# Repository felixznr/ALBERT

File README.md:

# ALBERT

Albert I was a rhesus macaque monkey and the first mammal launched on a rocket (V-2 Rocket "Blossom No. 3") on June 18, 1948. The launch was staged at Albert I, a nine-pound monkey, was anesthetized and placed inside the rocket's crew capsule in the nose of the V-2 rocket. The flight did not reach outer space. The last couple hours before his death, Albert was lit asf on morphine

---

## Project Overview

ALBERT is a self-regulating guided rocket project developed as a Maturaprojekt (Austrian graduation project). The goal is to build a fully functional, autonomous rocket system capable of correcting its own flight path and safely recovering via parachute deployment.

**Key Objectives:**
- Develop autonomous flight path correction through advanced control systems
- Implement fin-based steering for precise guidance
- Create a reliable parachute recovery system
- Design a concept of a custom solid fuel motor
- Integrate comprehensive telemetry and safety systems

## Team Structure

- **Timofey Luzin**: Recovery system, steering system, and structural components
- **Felix Zauner**: Flight computer development, control systems, simulation, and telemetry

## Repository Organization

```
├── 1_Documentation/        # Project documentation and requirements
├── 2_CAD_Structure/        # 3D models and structural designs  
├── 3_Flight_Computer/      # Flight computer hardware
├── 4_Simulation/           # Flight simulation and testing tools
└── 5_Codebase/             # Main source code and algorithms
```

For detailed technical specifications, see `1_Documentation/Diplomarbeit_ALBERT/chapter/main.pdf`.

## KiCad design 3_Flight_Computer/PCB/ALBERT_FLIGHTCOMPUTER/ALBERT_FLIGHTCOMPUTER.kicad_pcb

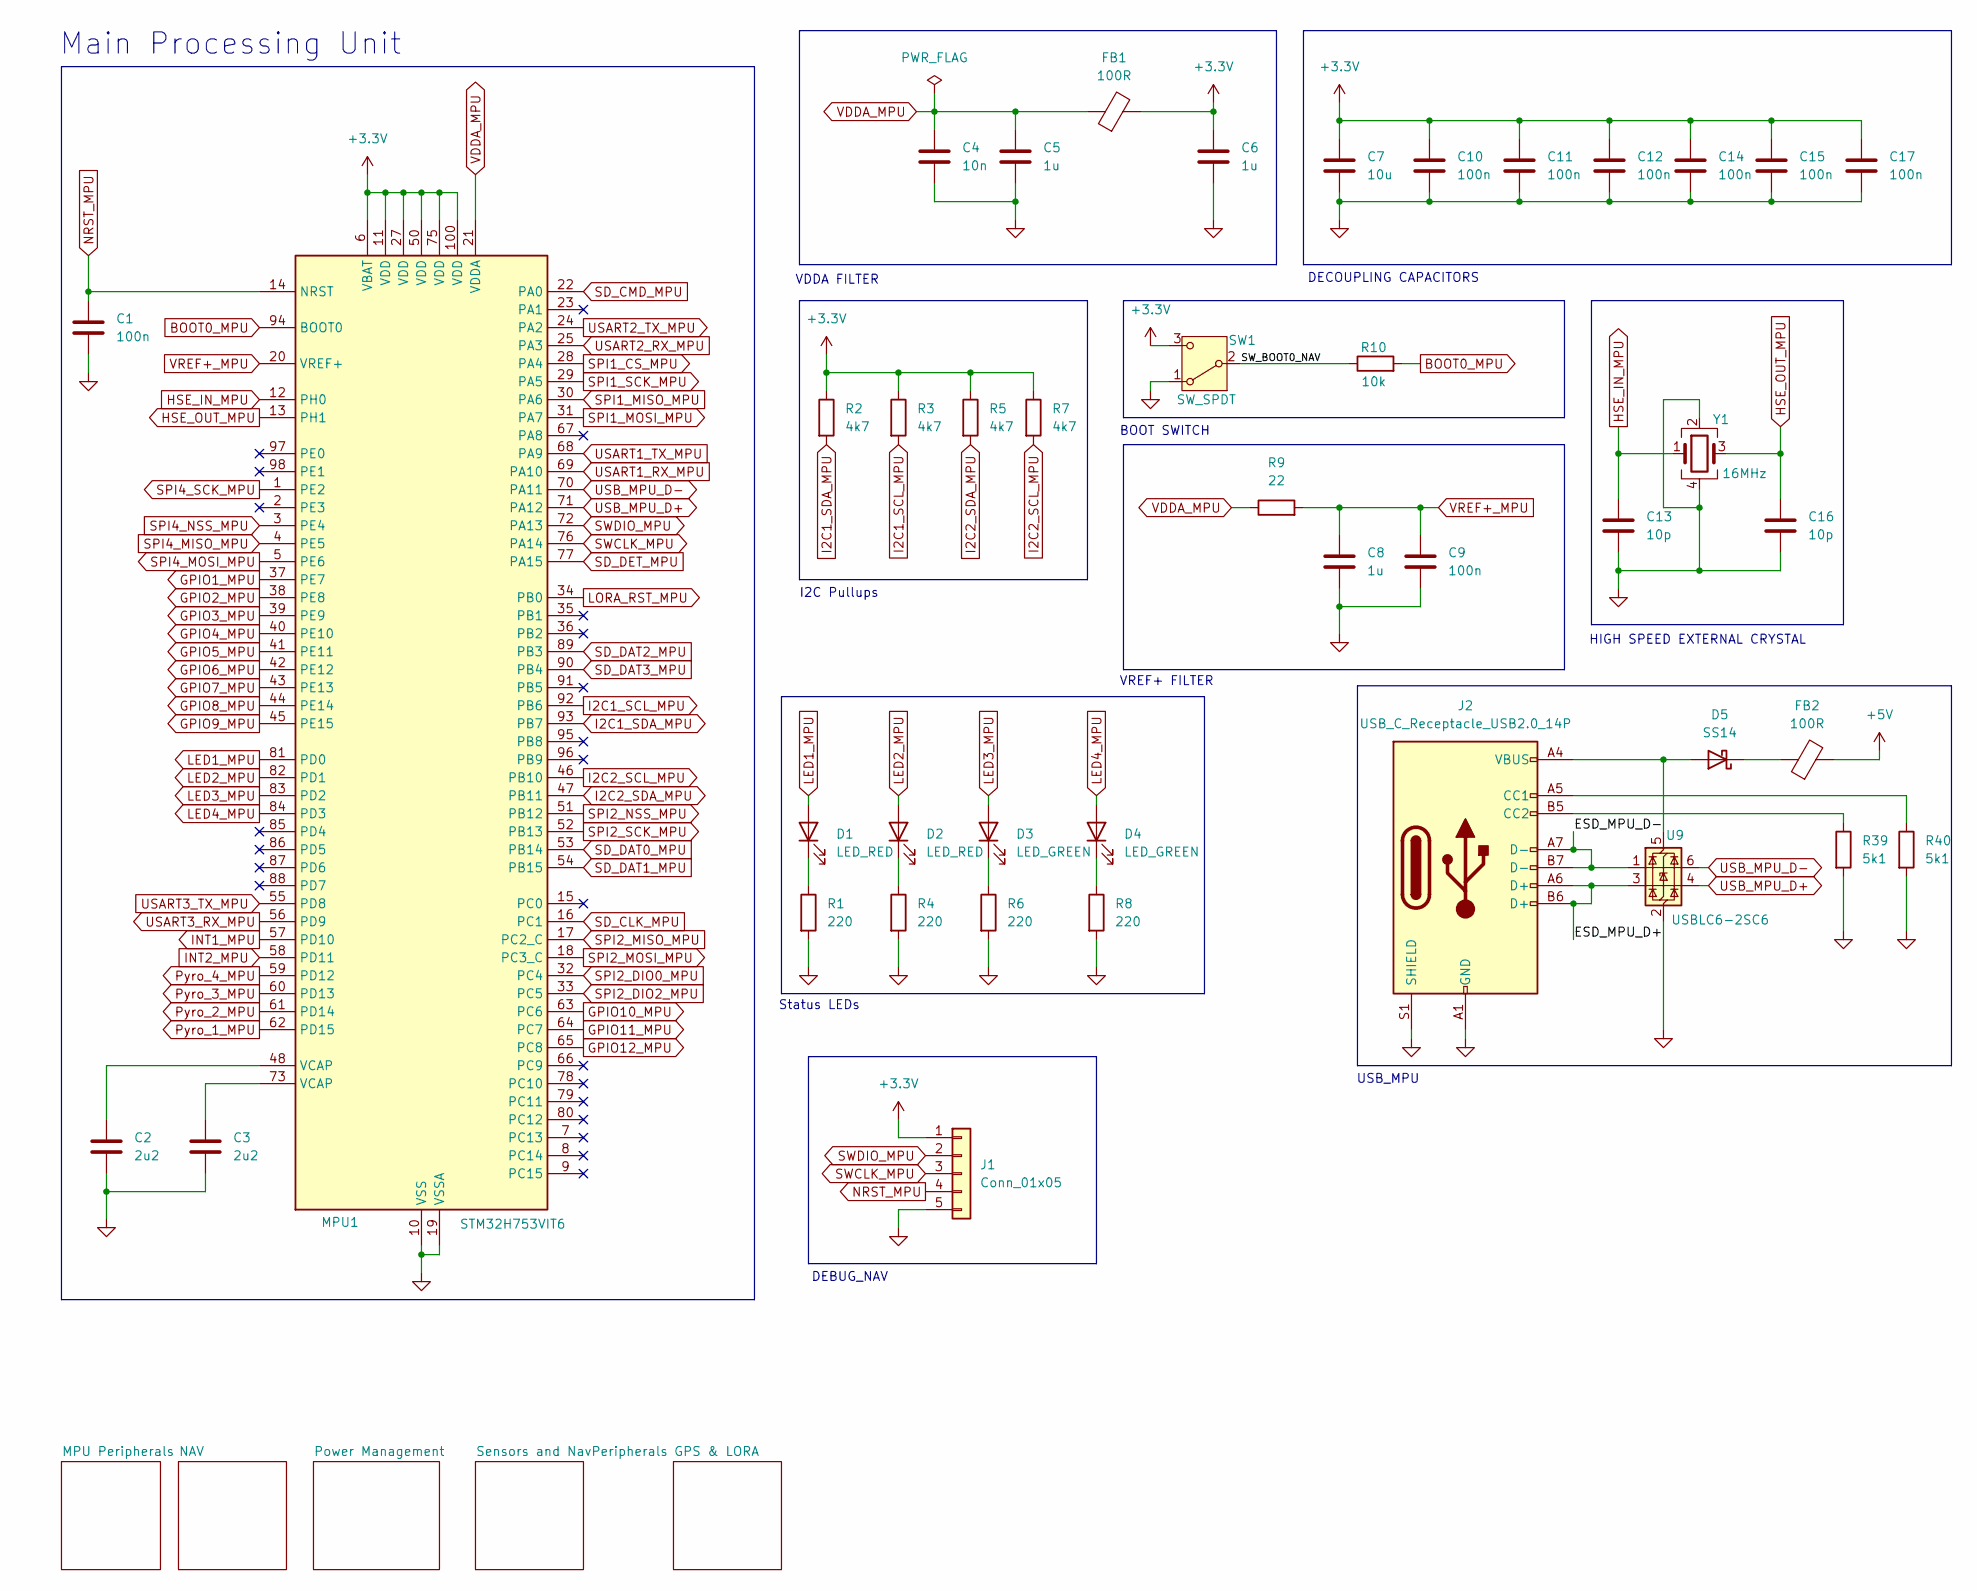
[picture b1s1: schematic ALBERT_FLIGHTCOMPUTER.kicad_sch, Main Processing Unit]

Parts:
C1, C9, C10, C11, C12, C14, C15, C17: 100n; C_0402_1005Metric; LCSC C1525
C2, C3: 2u2; C_0805_2012Metric; LCSC C377773
C4: 10n; C_0402_1005Metric; LCSC C15195
C5, C6, C8: 1u; C_0805_2012Metric; LCSC C28323
C7: 10u; C_0805_2012Metric; LCSC C15850
C13, C16: 10p; C_0402_1005Metric; LCSC C32949
D1, D2: LED_RED; LED_0603_1608Metric
D3, D4: LED_GREEN; LED_0603_1608Metric
D5: SS14; D_SMA; LCSC C2480
FB1: 100R; L_0603_1608Metric; LCSC C15957
FB2: 100R; L_0805_2012Metric; LCSC C15957
J1: Conn_01x05; PinHeader_1x05_P2.54mm_Vertical
J2: USB_C_Receptacle_USB2.0_14P; USB_C_Receptacle_HRO_TYPE-C-31-M-12; LCSC C165948
MPU1: STM32H753VIT6; LQFP-100_14x14mm_P0.5mm; Manufacturer Part Number STM32H753VIT6; LCSC C730206
R1, R4, R6, R8: 220; R_0402_1005Metric; LCSC C25091
R2, R3, R5, R7: 4k7; R_0402_1005Metric; LCSC C25900
R9: 22; R_0402_1005Metric; LCSC C25092
R10: 10k; R_0402_1005Metric; LCSC C25744
R39, R40: 5k1; R_0402_1005Metric; LCSC C25905
SW1: SW_SPDT; SW_SPDT_PCM12; LCSC C221841
U9: USBLC6-2SC6; SOT-23-6; LCSC C7519
Y1: 16MHz; Crystal_SMD_3225-4Pin_3.2x2.5mm; LCSC C13738

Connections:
+3.3V: C6.1, C7.1, C10.1, C11.1, C12.1, C14.1, C15.1, C17.1, FB1.2, J1.1, MPU1.6 (VBAT), MPU1.11 (VDD), MPU1.27 (VDD), MPU1.50 (VDD), MPU1.75 (VDD), MPU1.100 (VDD), R2.1, R3.1, R5.1, R7.1, SW1.3 (C); also elsewhere on the board
+5V: FB2.2; also elsewhere on the board
/ESD_MPU_D+: J2.A6 (D+), J2.B6 (D+), U9.3 (I/O2)
/ESD_MPU_D-: J2.A7 (D-), J2.B7 (D-), U9.1 (I/O1)
/SW_BOOT0_NAV: R10.1, SW1.2 (B)
BOOT0_MPU: MPU1.94 (BOOT0), R10.2
GND: C1.2, C2.2, C3.2, C4.2, C5.2, C6.2, C7.2, C8.2, C9.2, C10.2, C11.2, C12.2, C13.2, C14.2, C15.2, C16.2, C17.2, J1.5, J2.A1 (GND), J2.A12 (GND), J2.B1 (GND), J2.B12 (GND), J2.S1 (SHIELD), MPU1.10 (VSS), MPU1.19 (VSSA), MPU1.26 (VSS), MPU1.49 (VSS), MPU1.74 (VSS), MPU1.99 (VSS), R1.2, R4.2, R6.2, R8.2, R39.2, R40.2, SW1.1 (A), U9.2 (GND), Y1.2, Y1.4; also elsewhere on the board
GPIO1_MPU: MPU1.37 (PE7); also elsewhere on the board
GPIO2_MPU: MPU1.38 (PE8); also elsewhere on the board
GPIO3_MPU: MPU1.39 (PE9); also elsewhere on the board
GPIO4_MPU: MPU1.40 (PE10); also elsewhere on the board
GPIO5_MPU: MPU1.41 (PE11); also elsewhere on the board
GPIO6_MPU: MPU1.42 (PE12); also elsewhere on the board
GPIO7_MPU: MPU1.43 (PE13); also elsewhere on the board
GPIO8_MPU: MPU1.44 (PE14); also elsewhere on the board
GPIO9_MPU: MPU1.45 (PE15); also elsewhere on the board
GPIO10_MPU: MPU1.63 (PC6); also elsewhere on the board
GPIO11_MPU: MPU1.64 (PC7); also elsewhere on the board
GPIO12_MPU: MPU1.65 (PC8); also elsewhere on the board
HSE_IN_MPU: C13.1, MPU1.12 (PH0), Y1.1
HSE_OUT_MPU: C16.1, MPU1.13 (PH1), Y1.3
I2C1_SCL_MPU: MPU1.92 (PB6), R3.2; also elsewhere on the board
I2C1_SDA_MPU: MPU1.93 (PB7), R2.2; also elsewhere on the board
I2C2_SCL_MPU: MPU1.46 (PB10), R7.2; also elsewhere on the board
I2C2_SDA_MPU: MPU1.47 (PB11), R5.2; also elsewhere on the board
INT1_MPU: MPU1.57 (PD10); also elsewhere on the board
INT2_MPU: MPU1.58 (PD11); also elsewhere on the board
LED1_MPU: D1.2 (A), MPU1.81 (PD0)
LED2_MPU: D2.2 (A), MPU1.82 (PD1)
LED3_MPU: D3.2 (A), MPU1.83 (PD2)
LED4_MPU: D4.2 (A), MPU1.84 (PD3)
LORA_RST_MPU: MPU1.34 (PB0); also elsewhere on the board
NRST_MPU: C1.1, J1.4, MPU1.14 (NRST)
unnamed: C2.1, MPU1.48 (VCAP)
unnamed: C3.1, MPU1.73 (VCAP)
unnamed: D1.1 (K), R1.1
unnamed: D2.1 (K), R4.1
unnamed: D3.1 (K), R6.1
unnamed: D4.1 (K), R8.1
unnamed: D5.2 (A), J2.A4 (VBUS), J2.A9 (VBUS), J2.B4 (VBUS), J2.B9 (VBUS), U9.5 (VBUS)
unnamed: D5.1 (K), FB2.1
unnamed: J2.A5 (CC1), R40.1
unnamed: J2.B5 (CC2), R39.1
Pyro_1_MPU: MPU1.62 (PD15); also elsewhere on the board
Pyro_2_MPU: MPU1.61 (PD14); also elsewhere on the board
Pyro_3_MPU: MPU1.60 (PD13); also elsewhere on the board
Pyro_4_MPU: MPU1.59 (PD12); also elsewhere on the board
SD_CLK_MPU: MPU1.16 (PC1); also elsewhere on the board
SD_CMD_MPU: MPU1.22 (PA0); also elsewhere on the board
SD_DAT0_MPU: MPU1.53 (PB14); also elsewhere on the board
SD_DAT1_MPU: MPU1.54 (PB15); also elsewhere on the board
SD_DAT2_MPU: MPU1.89 (PB3); also elsewhere on the board
SD_DAT3_MPU: MPU1.90 (PB4); also elsewhere on the board
SD_DET_MPU: MPU1.77 (PA15); also elsewhere on the board
SPI1_CS_MPU: MPU1.28 (PA4); also elsewhere on the board
SPI1_MISO_MPU: MPU1.30 (PA6); also elsewhere on the board
SPI1_MOSI_MPU: MPU1.31 (PA7); also elsewhere on the board
SPI1_SCK_MPU: MPU1.29 (PA5); also elsewhere on the board
SPI2_DIO0_MPU: MPU1.32 (PC4); also elsewhere on the board
SPI2_DIO2_MPU: MPU1.33 (PC5); also elsewhere on the board
SPI2_MISO_MPU: MPU1.17 (PC2_C); also elsewhere on the board
SPI2_MOSI_MPU: MPU1.18 (PC3_C); also elsewhere on the board
SPI2_NSS_MPU: MPU1.51 (PB12); also elsewhere on the board
SPI2_SCK_MPU: MPU1.52 (PB13); also elsewhere on the board
SPI4_MISO_MPU: MPU1.4 (PE5); also elsewhere on the board
SPI4_MOSI_MPU: MPU1.5 (PE6); also elsewhere on the board
SPI4_NSS_MPU: MPU1.3 (PE4); also elsewhere on the board
SPI4_SCK_MPU: MPU1.1 (PE2); also elsewhere on the board
SWCLK_MPU: J1.3, MPU1.76 (PA14)
SWDIO_MPU: J1.2, MPU1.72 (PA13)
USART1_RX_MPU: MPU1.69 (PA10); also elsewhere on the board
USART1_TX_MPU: MPU1.68 (PA9); also elsewhere on the board
USART2_RX_MPU: MPU1.25 (PA3); also elsewhere on the board
USART2_TX_MPU: MPU1.24 (PA2); also elsewhere on the board
USART3_RX_MPU: MPU1.56 (PD9); also elsewhere on the board
USART3_TX_MPU: MPU1.55 (PD8); also elsewhere on the board
USB_MPU_D+: MPU1.71 (PA12), U9.4 (I/O2)
USB_MPU_D-: MPU1.70 (PA11), U9.6 (I/O1)
VDDA_MPU: C4.1, C5.1, FB1.1, MPU1.21 (VDDA), R9.1
VREF+_MPU: C8.1, C9.1, MPU1.20 (VREF+), R9.2

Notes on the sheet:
USB_MPU
BOOT SWITCH
VDDA FILTER
Main Processing Unit
VREF+ FILTER
I2C Pullups
DEBUG_NAV
HIGH SPEED EXTERNAL CRYSTAL
Status LEDs
DECOUPLING CAPACITORS

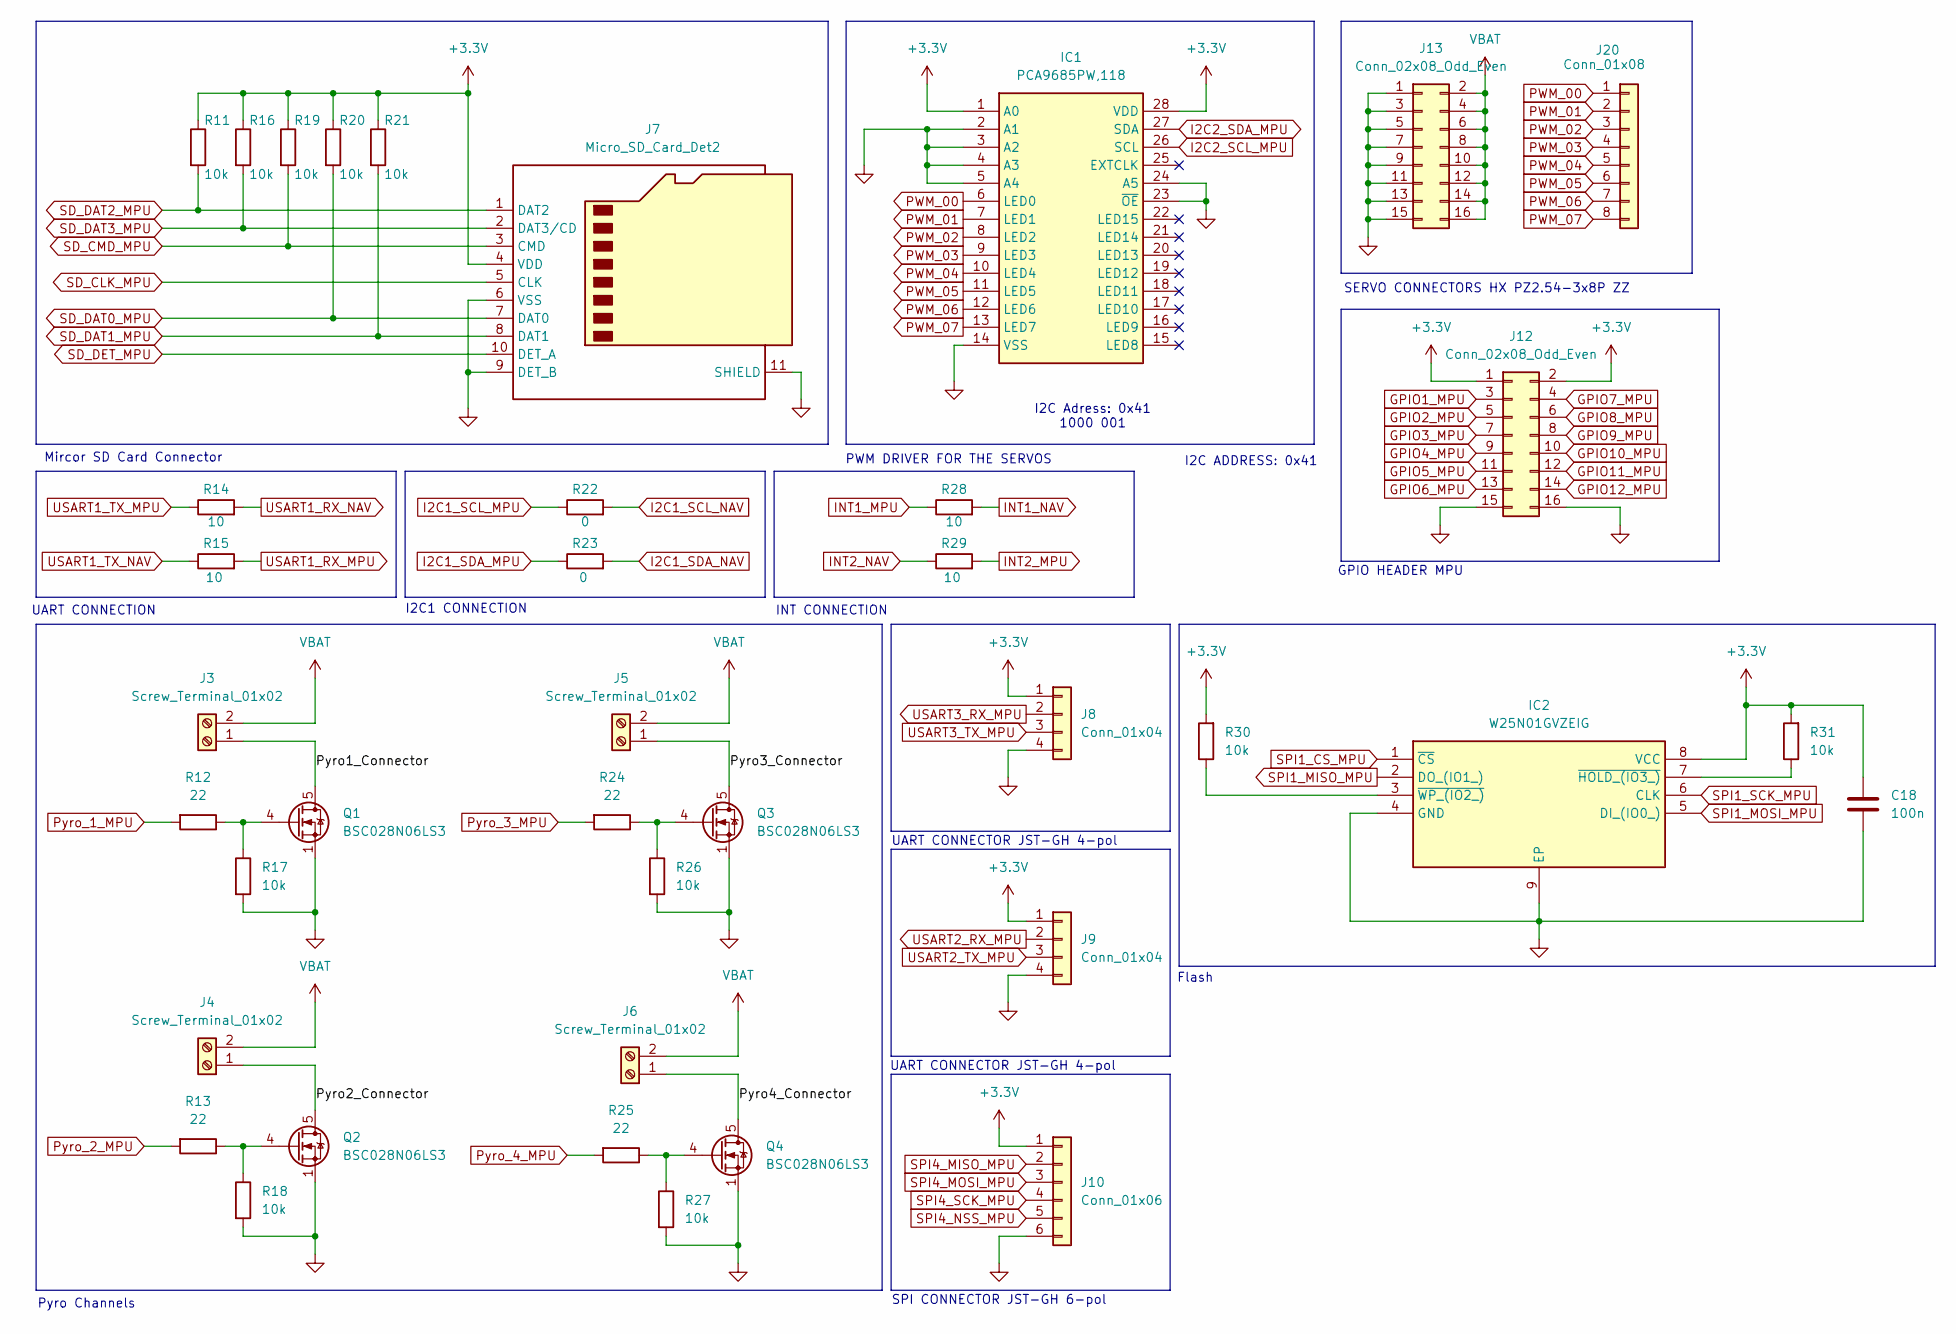
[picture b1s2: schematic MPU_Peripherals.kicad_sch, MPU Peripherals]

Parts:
C18: 100n; C_0402_1005Metric; LCSC C1525
IC1: PCA9685PW,118; SOP65P640X110-28N; Mouser Part Number 771-PCA9685PW,118
IC2: W25N01GVZEIG; SON127P800X600X80-9N-D; Mouser Part Number 454-W25N01GVZEIG
J3, J4, J5, J6: Screw_Terminal_01x02; TerminalBlock_Phoenix_MKDS-1,5-2-5.08_1x02_P5.08mm_Horizont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; LCSC C5183989
J7: Micro_SD_Card_Det2; microSD_HC_Hirose_DM3AT-SF-PEJM5; LCSC C114218
J8, J9: Conn_01x04; JST_PH_B4B-PH-K_1x04_P2.00mm_Vertical; LCSC C566011
J10: Conn_01x06; JST_PH_B6B-PH-K_1x06_P2.00mm_Vertical; LCSC C495261
J12, J13: Conn_02x08_Odd_Even; PinHeader_2x08_P2.54mm_Vertical
J20: Conn_01x08; PinHeader_1x08_P2.54mm_Vertical
Q1, Q2, Q3, Q4: BSC028N06LS3; TDSON-8-1; LCSC C534316
R11, R16, R17, R18, R19, R20, R21, R26, R27, R30, R31: 10k; R_0402_1005Metric; LCSC C25744
R12, R13, R24, R25: 22; R_0402_1005Metric; LCSC C25092
R14, R15, R28, R29: 10; R_0402_1005Metric; LCSC C25077
R22, R23: 0; R_0402_1005Metric; LCSC C17168

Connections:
+3.3V: C18.1, IC1.1 (A0), IC1.28 (VDD), IC2.8 (VCC), J7.4 (VDD), J8.1, J9.1, J10.1, J12.1, J12.2, R11.1, R16.1, R19.1, R20.1, R21.1, R30.2, R31.2; also elsewhere on the board
/MPU Peripherals/Pyro1_Connector: J3.1, Q1.5 (D)
/MPU Peripherals/Pyro2_Connector: J4.1, Q2.5 (D)
/MPU Peripherals/Pyro3_Connector: J5.1, Q3.5 (D)
/MPU Peripherals/Pyro4_Connector: J6.1, Q4.5 (D)
GND: C18.2, IC1.2 (A1), IC1.3 (A2), IC1.4 (A3), IC1.5 (A4), IC1.14 (VSS), IC1.23 (~OE), IC1.24 (A5), IC2.4 (GND), IC2.9 (EP), J7.6 (VSS), J7.9 (DET_B), J7.11 (SHIELD), J8.4, J9.4, J10.6, J12.15, J12.16, J13.1, J13.3, J13.5, J13.7, J13.9, J13.11, J13.13, J13.15, Q1.1 (S), Q1.2 (S), Q1.3 (S), Q2.1 (S), Q2.2 (S), Q2.3 (S), Q3.1 (S), Q3.2 (S), Q3.3 (S), Q4.1 (S), Q4.2 (S), Q4.3 (S), R17.2, R18.2, R26.2, R27.2; also elsewhere on the board
GPIO1_MPU: J12.3; also elsewhere on the board
GPIO2_MPU: J12.5; also elsewhere on the board
GPIO3_MPU: J12.7; also elsewhere on the board
GPIO4_MPU: J12.9; also elsewhere on the board
GPIO5_MPU: J12.11; also elsewhere on the board
GPIO6_MPU: J12.13; also elsewhere on the board
GPIO7_MPU: J12.4; also elsewhere on the board
GPIO8_MPU: J12.6; also elsewhere on the board
GPIO9_MPU: J12.8; also elsewhere on the board
GPIO10_MPU: J12.10; also elsewhere on the board
GPIO11_MPU: J12.12; also elsewhere on the board
GPIO12_MPU: J12.14; also elsewhere on the board
I2C1_SCL_MPU: R22.1; also elsewhere on the board
I2C1_SCL_NAV: R22.2; also elsewhere on the board
I2C1_SDA_MPU: R23.1; also elsewhere on the board
I2C1_SDA_NAV: R23.2; also elsewhere on the board
I2C2_SCL_MPU: IC1.26 (SCL); also elsewhere on the board
I2C2_SDA_MPU: IC1.27 (SDA); also elsewhere on the board
IN-: J3.2, J4.2, J5.2, J6.2, J13.2, J13.4, J13.6, J13.8, J13.10, J13.12, J13.14, J13.16; also elsewhere on the board
INT1_MPU: R28.1; also elsewhere on the board
INT1_NAV: R28.2; also elsewhere on the board
INT2_MPU: R29.2; also elsewhere on the board
INT2_NAV: R29.1; also elsewhere on the board
unnamed: IC2.7 (~HOLD_(IO3_)), R31.1
unnamed: IC2.3 (~WP_(IO2_)), R30.1
unnamed: Q1.4 (G), R12.1, R17.1
unnamed: Q2.4 (G), R13.1, R18.1
unnamed: Q3.4 (G), R24.1, R26.1
unnamed: Q4.4 (G), R25.1, R27.1
PWM_00: IC1.6 (LED0), J20.1
PWM_01: IC1.7 (LED1), J20.2
PWM_02: IC1.8 (LED2), J20.3
PWM_03: IC1.9 (LED3), J20.4
PWM_04: IC1.10 (LED4), J20.5
PWM_05: IC1.11 (LED5), J20.6
PWM_06: IC1.12 (LED6), J20.7
PWM_07: IC1.13 (LED7), J20.8
Pyro_1_MPU: R12.2; also elsewhere on the board
Pyro_2_MPU: R13.2; also elsewhere on the board
Pyro_3_MPU: R24.2; also elsewhere on the board
Pyro_4_MPU: R25.2; also elsewhere on the board
SD_CLK_MPU: J7.5 (CLK); also elsewhere on the board
SD_CMD_MPU: J7.3 (CMD), R19.2; also elsewhere on the board
SD_DAT0_MPU: J7.7 (DAT0), R20.2; also elsewhere on the board
SD_DAT1_MPU: J7.8 (DAT1), R21.2; also elsewhere on the board
SD_DAT2_MPU: J7.1 (DAT2), R11.2; also elsewhere on the board
SD_DAT3_MPU: J7.2 (DAT3/CD), R16.2; also elsewhere on the board
SD_DET_MPU: J7.10 (DET_A); also elsewhere on the board
SPI1_CS_MPU: IC2.1 (~CS); also elsewhere on the board
SPI1_MISO_MPU: IC2.2 (DO_(IO1_)); also elsewhere on the board
SPI1_MOSI_MPU: IC2.5 (DI_(IO0_)); also elsewhere on the board
SPI1_SCK_MPU: IC2.6 (CLK); also elsewhere on the board
SPI4_MISO_MPU: J10.2; also elsewhere on the board
SPI4_MOSI_MPU: J10.3; also elsewhere on the board
SPI4_NSS_MPU: J10.5; also elsewhere on the board
SPI4_SCK_MPU: J10.4; also elsewhere on the board
USART1_RX_MPU: R15.2; also elsewhere on the board
USART1_RX_NAV: R14.2; also elsewhere on the board
USART1_TX_MPU: R14.1; also elsewhere on the board
USART1_TX_NAV: R15.1; also elsewhere on the board
USART2_RX_MPU: J9.2; also elsewhere on the board
USART2_TX_MPU: J9.3; also elsewhere on the board
USART3_RX_MPU: J8.2; also elsewhere on the board
USART3_TX_MPU: J8.3; also elsewhere on the board

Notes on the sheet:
I2C ADDRESS: 0x41
GPIO HEADER MPU
INT CONNECTION
UART CONNECTOR JST-GH 4-pol
Mircor SD Card Connector
SPI CONNECTOR JST-GH 6-pol
I2C Adress: 0x41 1000 001
PWM DRIVER FOR THE SERVOS
Flash
Pyro Channels
SERVO CONNECTORS HX PZ2.54-3x8P ZZ
UART CONNECTION
I2C1 CONNECTION

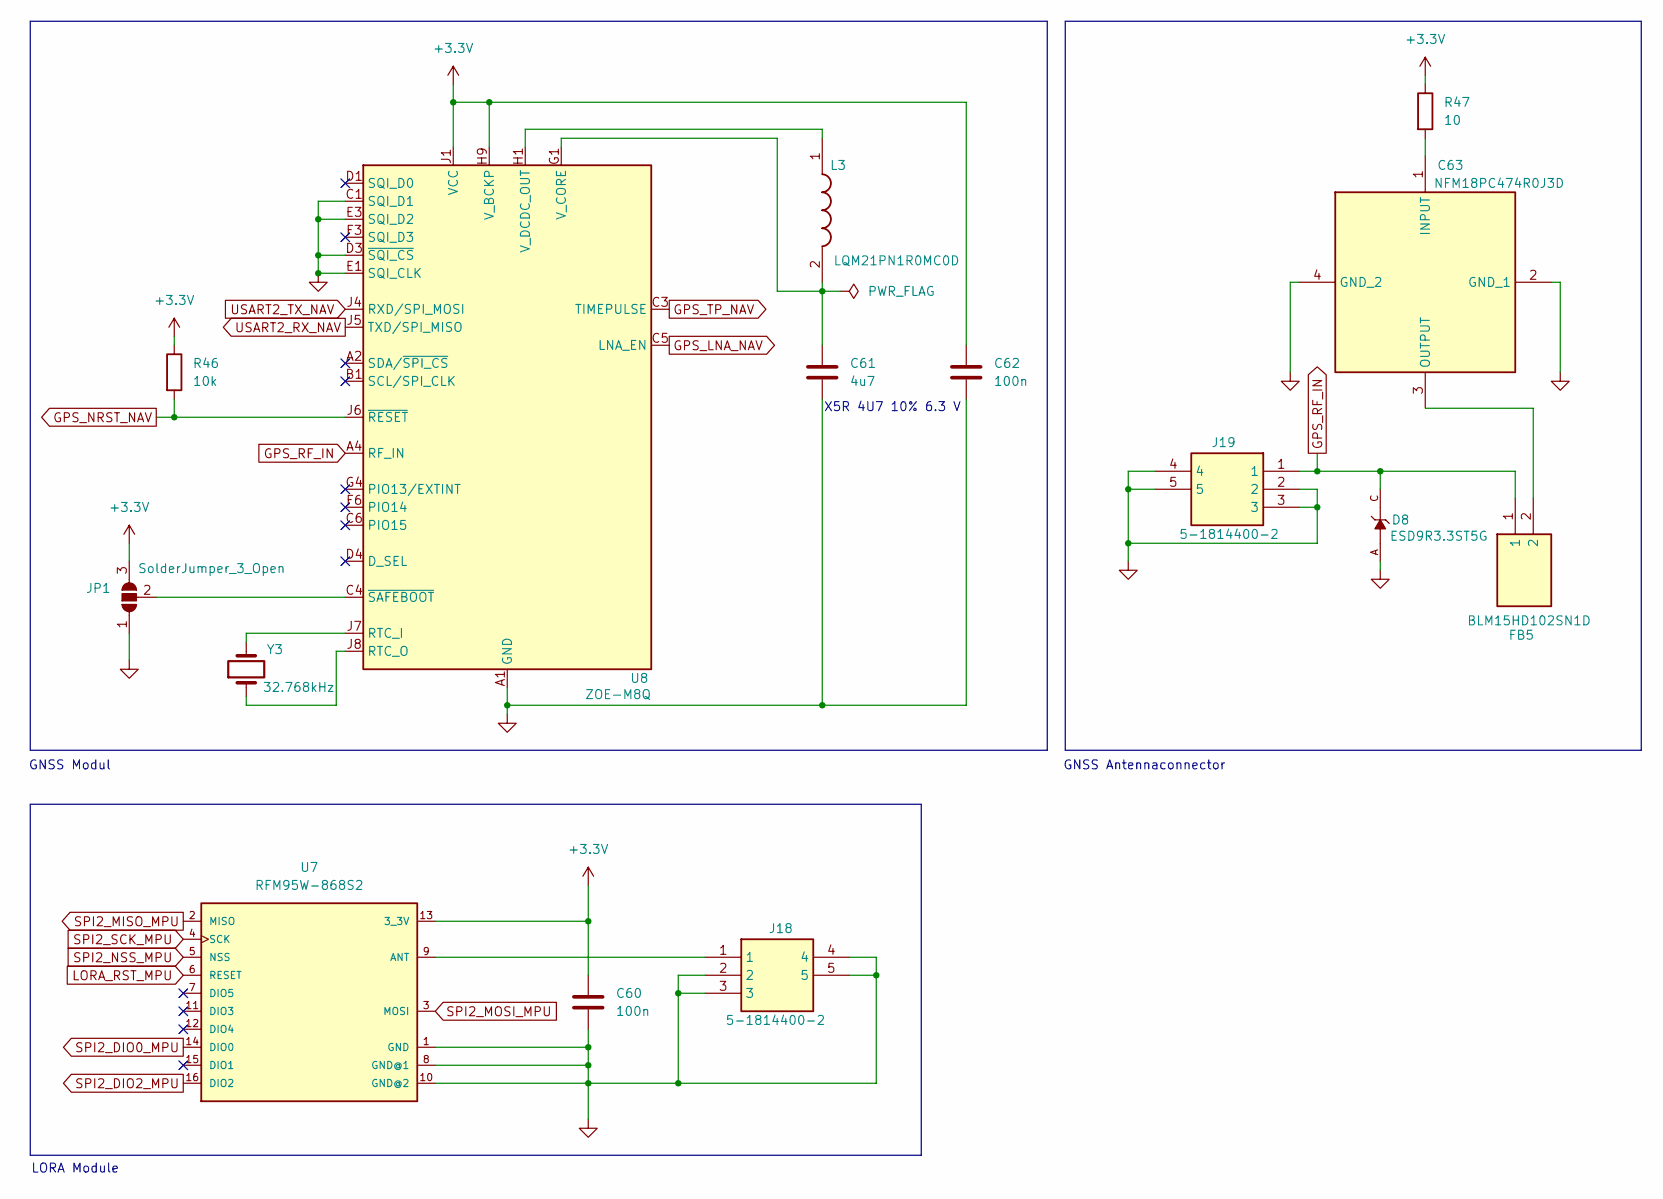
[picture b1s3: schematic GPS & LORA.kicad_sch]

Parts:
C60, C62: 100n; C_0402_1005Metric; LCSC C1525
C61: 4u7; CAPC2012X135N; LCSC C1746
C63: NFM18PC474R0J3D; Mouser Part Number 81-NFM18PC474R0J3D
D8: ESD9R3.3ST5G; SODFL1006X40N; PARTREV 2; LCSC C233388
FB5: BLM15HD102SN1D; NFZ15SG152SN10B; Mouser Part Number 81-BLM15HD102SN1D
J18, J19: 5-1814400-2; 518144002; Mouser Part Number 571-5-1814400-2
JP1: SolderJumper_3_Open; SolderJumper-3_P1.3mm_Open_RoundedPad1.0x1.5mm_NumberLabels
L3: LQM21PN1R0MC0D; Mouser Part Number 81-LQM21PN1R0MC0D
R46: 10k; R_0402_1005Metric; LCSC C25744
R47: 10; R_0402_1005Metric; LCSC C25077
U7: RFM95W-868S2; XCVR_RFM95W-868S2
U8: ZOE-M8Q; ublox_ZOE_M8; LCSC C7398634
Y3: 32.768kHz; Crystal_SMD_MicroCrystal_CC7V-T1A-2Pin_3.2x1.5mm; LCSC C7462182

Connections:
+3.3V: C60.1, C62.1, JP1.3 (B), R46.1, R47.1, U7.13 (3_3V), U8.H9 (V_BCKP), U8.J1 (VCC), U8.J2 (VCC); also elsewhere on the board
GND: C60.2, C61.2, C62.2, C63.2 (GND_1), C63.4 (GND_2), D8.A, J18.2, J18.3, J18.4, J18.5, J19.2, J19.3, J19.4, J19.5, JP1.1 (A), U7.1 (GND), U7.8 (GND@1), U7.10 (GND@2), U8.A1 (GND), U8.A3 (GND), U8.A5 (GND), U8.A7 (GND), U8.A8 (GND), U8.A9 (GND), U8.B9 (GND), U8.C1 (SQI_D1), U8.C7 (GND), U8.C9 (GND), U8.D3 (~SQI_CS), U8.D6 (GND), U8.D9 (GND), U8.E1 (SQI_CLK), U8.E3 (SQI_D2), U8.E7 (GND), U8.F7 (GND), U8.G3 (GND), U8.G6 (GND), U8.G7 (GND), U8.J3 (GND), U8.J9 (GND); also elsewhere on the board
GPS_LNA_NAV: U8.C5 (LNA_EN); also elsewhere on the board
GPS_NRST_NAV: R46.2, U8.J6 (~RESET)
GPS_RF_IN: D8.C, FB5.1, J19.1, U8.A4 (RF_IN)
GPS_TP_NAV: U8.C3 (TIMEPULSE); also elsewhere on the board
LORA_RST_MPU: U7.6 (RESET); also elsewhere on the board
unnamed: C63.1 (INPUT), R47.2
unnamed: C63.3 (OUTPUT), FB5.2
unnamed: JP1.2 (B), U8.C4 (~SAFEBOOT)
unnamed: J18.1, U7.9 (ANT)
unnamed: U8.J7 (RTC_I), Y3.2
unnamed: U8.J8 (RTC_O), Y3.1
unnamed: C61.1, L3.2, U8.G1 (V_CORE)
unnamed: L3.1, U8.H1 (V_DCDC_OUT)
SPI2_DIO0_MPU: U7.14 (DIO0); also elsewhere on the board
SPI2_DIO2_MPU: U7.16 (DIO2); also elsewhere on the board
SPI2_MISO_MPU: U7.2 (MISO); also elsewhere on the board
SPI2_MOSI_MPU: U7.3 (MOSI); also elsewhere on the board
SPI2_NSS_MPU: U7.5 (NSS); also elsewhere on the board
SPI2_SCK_MPU: U7.4 (SCK); also elsewhere on the board
USART2_RX_NAV: U8.J5 (TXD/SPI_MISO); also elsewhere on the board
USART2_TX_NAV: U8.J4 (RXD/SPI_MOSI); also elsewhere on the board

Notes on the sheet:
GNSS Antennaconnector
GNSS Modul
LORA Module
X5R 4U7 10% 6.3 V

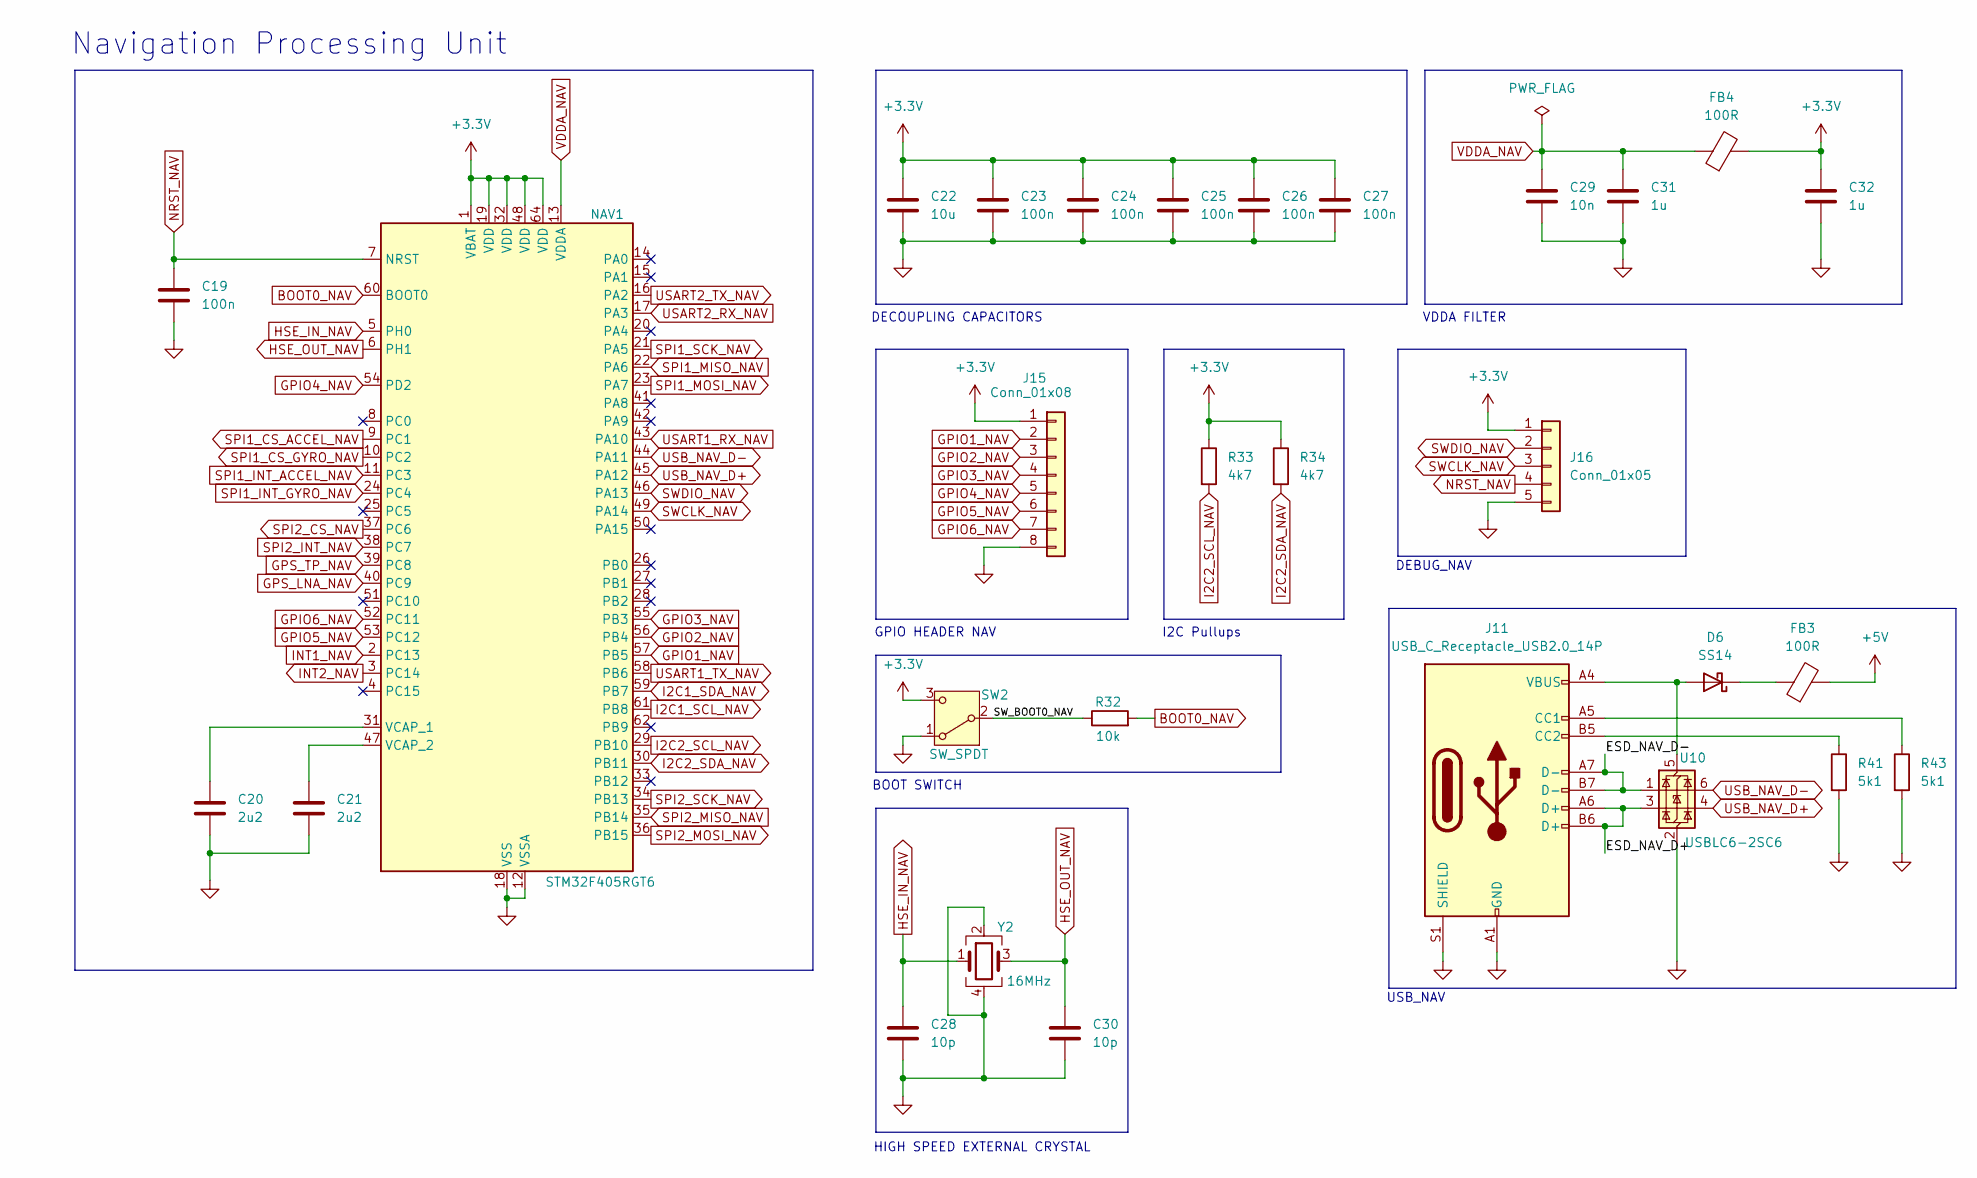
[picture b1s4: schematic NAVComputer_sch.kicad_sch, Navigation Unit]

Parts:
C19, C23, C24, C25, C26, C27: 100n; C_0402_1005Metric; LCSC C1525
C20, C21: 2u2; C_0805_2012Metric; LCSC C377773
C22: 10u; C_0805_2012Metric; LCSC C15850
C28, C30: 10p; C_0402_1005Metric; LCSC C32949
C29: 10n; C_0402_1005Metric; LCSC C15195
C31, C32: 1u; C_0805_2012Metric; LCSC C28323
D6: SS14; D_SMA; LCSC C2480
FB3, FB4: 100R; L_0805_2012Metric; LCSC C15957
J11: USB_C_Receptacle_USB2.0_14P; USB_C_Receptacle_HRO_TYPE-C-31-M-12; LCSC C165948
J15: Conn_01x08; PinHeader_1x08_P2.54mm_Vertical
J16: Conn_01x05; PinHeader_1x05_P2.54mm_Vertical
NAV1: STM32F405RGT6; LQFP-64_10x10mm_P0.5mm; LCSC C15742
R32: 10k; R_0402_1005Metric; LCSC C25744
R33, R34: 4k7; R_0402_1005Metric; LCSC C25900
R41, R43: 5k1; R_0402_1005Metric; LCSC C25905
SW2: SW_SPDT; SW_SPDT_PCM12; LCSC C221841
U10: USBLC6-2SC6; SOT-23-6; LCSC C7519
Y2: 16MHz; Crystal_SMD_3225-4Pin_3.2x2.5mm; LCSC C13738

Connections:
+3.3V: C22.1, C23.1, C24.1, C25.1, C26.1, C27.1, C32.1, FB4.2, J15.1, J16.1, NAV1.1 (VBAT), NAV1.19 (VDD), NAV1.32 (VDD), NAV1.48 (VDD), NAV1.64 (VDD), R33.1, R34.1, SW2.3 (C); also elsewhere on the board
+5V: FB3.2; also elsewhere on the board
/NAV/ESD_NAV_D+: J11.A6 (D+), J11.B6 (D+), U10.3 (I/O2)
/NAV/ESD_NAV_D-: J11.A7 (D-), J11.B7 (D-), U10.1 (I/O1)
/NAV/SW_BOOT0_NAV: R32.1, SW2.2 (B)
BOOT0_NAV: NAV1.60 (BOOT0), R32.2
GND: C19.2, C20.2, C21.2, C22.2, C23.2, C24.2, C25.2, C26.2, C27.2, C28.2, C29.2, C30.2, C31.2, C32.2, J11.A1 (GND), J11.A12 (GND), J11.B1 (GND), J11.B12 (GND), J11.S1 (SHIELD), J15.8, J16.5, NAV1.12 (VSSA), NAV1.18 (VSS), NAV1.63 (VSS), R41.2, R43.2, SW2.1 (A), U10.2 (GND), Y2.2, Y2.4; also elsewhere on the board
GPIO1_NAV: J15.2, NAV1.57 (PB5)
GPIO2_NAV: J15.3, NAV1.56 (PB4)
GPIO3_NAV: J15.4, NAV1.55 (PB3)
GPIO4_NAV: J15.5, NAV1.54 (PD2)
GPIO5_NAV: J15.6, NAV1.53 (PC12)
GPIO6_NAV: J15.7, NAV1.52 (PC11)
GPS_LNA_NAV: NAV1.40 (PC9); also elsewhere on the board
GPS_TP_NAV: NAV1.39 (PC8); also elsewhere on the board
HSE_IN_NAV: C28.1, NAV1.5 (PH0), Y2.1
HSE_OUT_NAV: C30.1, NAV1.6 (PH1), Y2.3
I2C1_SCL_NAV: NAV1.61 (PB8); also elsewhere on the board
I2C1_SDA_NAV: NAV1.59 (PB7); also elsewhere on the board
I2C2_SCL_NAV: NAV1.29 (PB10), R33.2; also elsewhere on the board
I2C2_SDA_NAV: NAV1.30 (PB11), R34.2; also elsewhere on the board
INT1_NAV: NAV1.2 (PC13); also elsewhere on the board
INT2_NAV: NAV1.3 (PC14); also elsewhere on the board
NRST_NAV: C19.1, J16.4, NAV1.7 (NRST)
unnamed: D6.2 (A), J11.A4 (VBUS), J11.A9 (VBUS), J11.B4 (VBUS), J11.B9 (VBUS), U10.5 (VBUS)
unnamed: D6.1 (K), FB3.1
unnamed: J11.A5 (CC1), R43.1
unnamed: J11.B5 (CC2), R41.1
unnamed: C20.1, NAV1.31 (VCAP_1)
unnamed: C21.1, NAV1.47 (VCAP_2)
SPI1_CS_ACCEL_NAV: NAV1.9 (PC1); also elsewhere on the board
SPI1_CS_GYRO_NAV: NAV1.10 (PC2); also elsewhere on the board
SPI1_INT_ACCEL_NAV: NAV1.11 (PC3); also elsewhere on the board
SPI1_INT_GYRO_NAV: NAV1.24 (PC4); also elsewhere on the board
SPI1_MISO_NAV: NAV1.22 (PA6); also elsewhere on the board
SPI1_MOSI_NAV: NAV1.23 (PA7); also elsewhere on the board
SPI1_SCK_NAV: NAV1.21 (PA5); also elsewhere on the board
SPI2_CS_NAV: NAV1.37 (PC6); also elsewhere on the board
SPI2_INT_NAV: NAV1.38 (PC7); also elsewhere on the board
SPI2_MISO_NAV: NAV1.35 (PB14); also elsewhere on the board
SPI2_MOSI_NAV: NAV1.36 (PB15); also elsewhere on the board
SPI2_SCK_NAV: NAV1.34 (PB13); also elsewhere on the board
SWCLK_NAV: J16.3, NAV1.49 (PA14)
SWDIO_NAV: J16.2, NAV1.46 (PA13)
USART1_RX_NAV: NAV1.43 (PA10); also elsewhere on the board
USART1_TX_NAV: NAV1.58 (PB6); also elsewhere on the board
USART2_RX_NAV: NAV1.17 (PA3); also elsewhere on the board
USART2_TX_NAV: NAV1.16 (PA2); also elsewhere on the board
USB_NAV_D+: NAV1.45 (PA12), U10.4 (I/O2)
USB_NAV_D-: NAV1.44 (PA11), U10.6 (I/O1)
VDDA_NAV: C29.1, C31.1, FB4.1, NAV1.13 (VDDA)

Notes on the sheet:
BOOT SWITCH
I2C Pullups
USB_NAV
Navigation Processing Unit
VDDA FILTER
GPIO HEADER NAV
DECOUPLING CAPACITORS
HIGH SPEED EXTERNAL CRYSTAL
DEBUG_NAV
